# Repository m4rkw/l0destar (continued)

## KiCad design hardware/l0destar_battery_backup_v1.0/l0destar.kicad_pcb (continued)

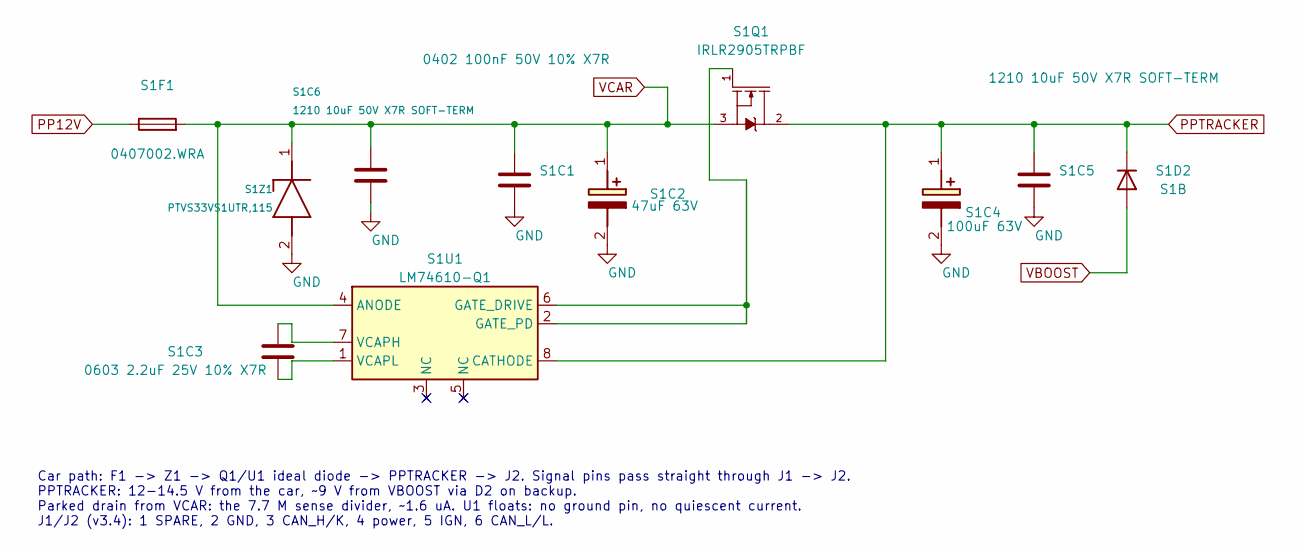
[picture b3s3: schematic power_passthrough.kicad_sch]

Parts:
S1C1: 0402 100nF 50V 10% X7R; C_0402_1005Metric; MPN GRM155R71H104KE14D
S1C2: 47uF 63V; EEE_FK1J470P; MPN EEE-FK1J470P
S1C3: 0603 2.2uF 25V 10% X7R; C_0603_1608Metric; MPN GRM188Z71E225KE43D
S1C4: 100uF 63V; EEEFK1J101P; MPN EEE-FK1J101P
S1C5, S1C6: 1210 10uF 50V X7R SOFT-TERM; C_1210_3225Metric; MPN MCJCU32MLB7106KPPDT1
S1D2: S1B; D_SMA; MPN S1B
S1F1: 0407002.WRA; Fuse_1206_3216Metric; MPN 0407002.WRA
S1Q1: IRLR2905TRPBF
S1U1: LM74610-Q1; VSSOP-8_3x3mm_P0.65mm; MPN LM74610QDGKRQ1
S1Z1: PTVS33VS1UTR,115; Nexperia_CFP3_SOD-123W; MPN PTVS33VS1UTR,115

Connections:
GND: S1C1.2, S1C2.2 (-), S1C4.2 (-), S1C5.2, S1C6.2, S1Z1.2 (A); also elsewhere on the board
unnamed: S1Q1.1, S1U1.2 (GATE_PD), S1U1.6 (GATE_DRIVE)
unnamed: S1C3.1, S1U1.7 (VCAPH)
unnamed: S1C3.2, S1U1.1 (VCAPL)
PP12V: S1F1.1; also elsewhere on the board
PPTRACKER: S1C4.1 (+), S1C5.1, S1D2.1 (K), S1Q1.2, S1Q1.PAD, S1U1.8 (CATHODE); also elsewhere on the board
VBOOST: S1D2.2 (A); also elsewhere on the board
VCAR: S1C1.1, S1C2.1 (+), S1C6.1, S1F1.2, S1Q1.3, S1U1.4 (ANODE), S1Z1.1 (K); also elsewhere on the board

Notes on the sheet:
Car path: F1 -> Z1 -> Q1/U1 ideal diode -> PPTRACKER -> J2. Signal pins pass straight through J1 -> J2. PPTRACKER: 12-14.5 V from the car, ~9 V from VBOOST via D2 on backup. Parked drain from VCAR: the 7.7 M sense divider, ~1.6 uA. U1 floats: no ground pin, no quiescent current. J1/J2 (v3.4): 1 SPA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

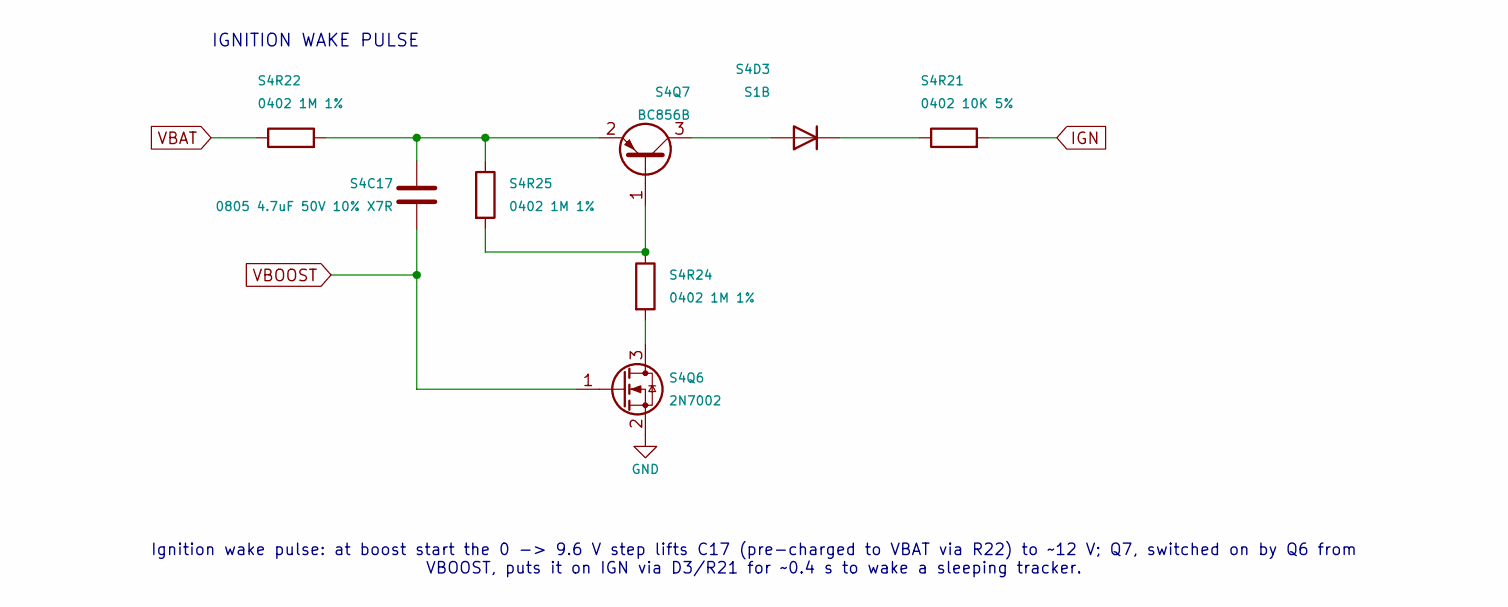
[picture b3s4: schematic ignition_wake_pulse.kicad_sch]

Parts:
S4C17: 0805 4.7uF 50V 10% X7R; C_0805_2012Metric; MPN GRM21BZ71H475KE15K
S4D3: S1B; D_SMA; MPN S1B
S4Q6: 2N7002; SOT-23; MPN 2N7002
S4Q7: BC856B; SOT-23; MPN BC856B
S4R21: 0402 10K 5%; R_0402_1005Metric
S4R22, S4R24, S4R25: 0402 1M 1%; R_0402_1005Metric

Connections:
GND: S4Q6.2 (S); also elsewhere on the board
IGN: S4R21.2; also elsewhere on the board
unnamed: S4D3.2 (A), S4Q7.3 (C)
unnamed: S4D3.1 (K), S4R21.1
unnamed: S4Q6.3 (D), S4R24.2
unnamed: S4Q7.1 (B), S4R24.1, S4R25.2
unnamed: S4C17.1, S4Q7.2 (E), S4R22.2, S4R25.1
VBAT: S4R22.1; also elsewhere on the board
VBOOST: S4C17.2, S4Q6.1 (G); also elsewhere on the board

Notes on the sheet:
IGNITION WAKE PULSE
Ignition wake pulse: at boost start the 0 -> 9.6 V step lifts C17 (pre-charged to VBAT via R22) to ~12 V; Q7, switched on by Q6 from VBOOST, puts it on IGN via D3/R21 for ~0.4 s to wake a sleeping tracker.

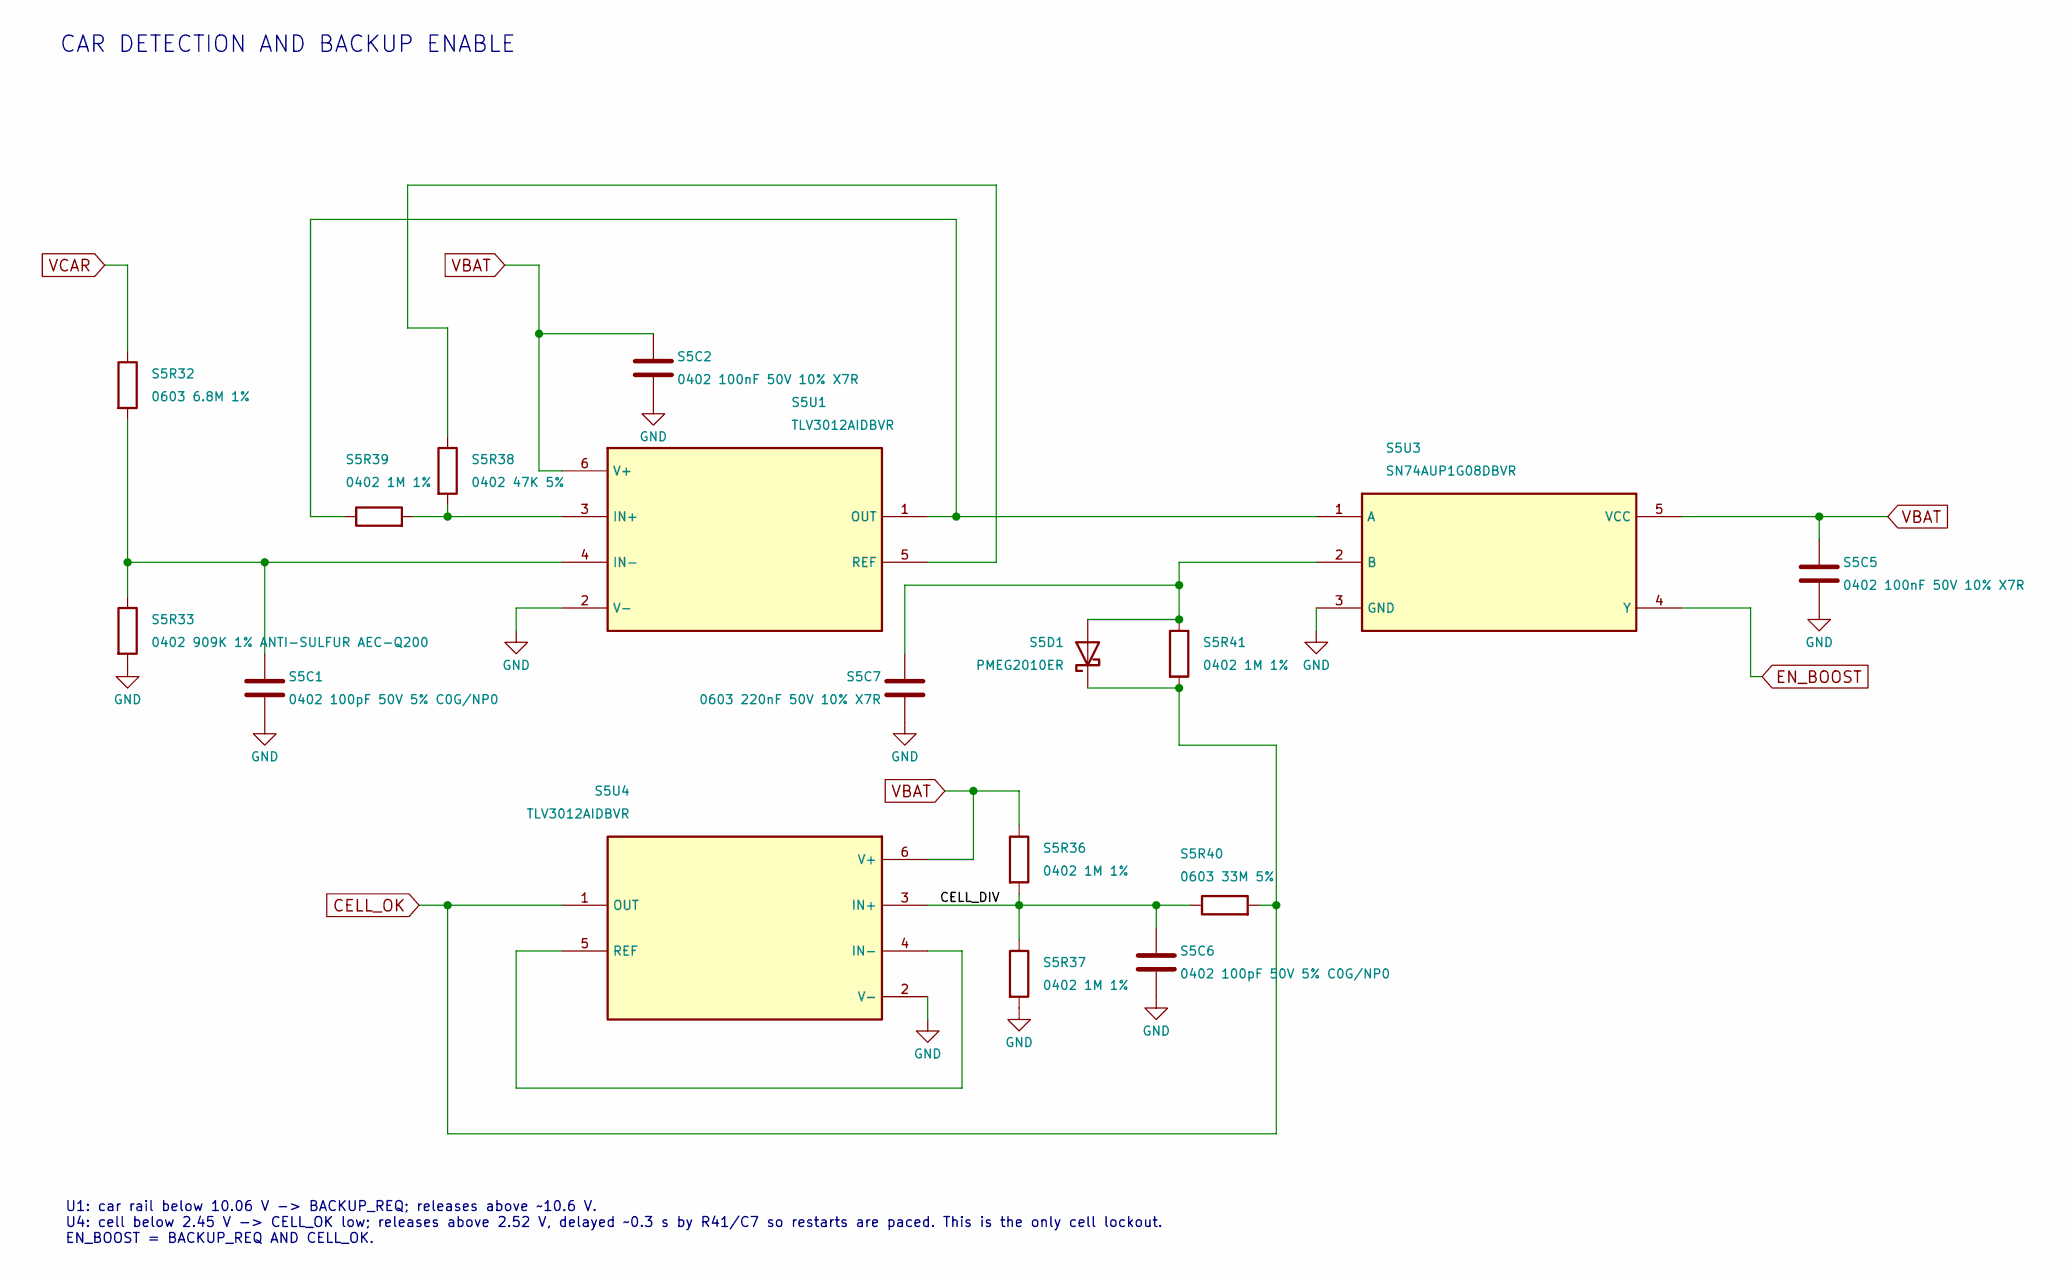
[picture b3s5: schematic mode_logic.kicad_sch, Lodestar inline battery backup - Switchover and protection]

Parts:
S5C1, S5C6: 0402 100pF 50V 5% C0G/NP0; C_0402_1005Metric; MPN 0402N101J500CT
S5C2, S5C5: 0402 100nF 50V 10% X7R; C_0402_1005Metric; MPN GRM155R71H104KE14D
S5C7: 0603 220nF 50V 10% X7R; C_0603_1608Metric
S5D1: PMEG2010ER; Nexperia_CFP3_SOD-123W; MPN PMEG2010ER,115
S5R32: 0603 6.8M 1%; R_0603_1608Metric
S5R33: 0402 909K 1% ANTI-SULFUR AEC-Q200; R_0402_1005Metric; MPN AF0402FR-07909KL
S5R36, S5R37, S5R39, S5R41: 0402 1M 1%; R_0402_1005Metric
S5R38: 0402 47K 5%; R_0402_1005Metric
S5R40: 0603 33M 5%; R_0603_1608Metric
S5U1, S5U4: TLV3012AIDBVR; SOT-23-6; MPN TLV3012AIDBVR
S5U3: SN74AUP1G08DBVR; SOT-23-5; MPN SN74AUP1G08DBVR

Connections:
/Automatic switchover/CELL_DIV: S5C6.1, S5R36.2, S5R37.1, S5R40.1, S5U4.3 (IN+)
CELL_OK: S5D1.1 (K), S5R40.2, S5R41.2, S5U4.1 (OUT)
EN_BOOST: S5U3.4 (Y); also elsewhere on the board
GND: S5C1.2, S5C2.2, S5C5.2, S5C6.2, S5C7.2, S5R33.2, S5R37.2, S5U1.2 (V-), S5U3.3 (GND), S5U4.2 (V-); also elsewhere on the board
unnamed: S5C7.1, S5D1.2 (A), S5R41.1, S5U3.2 (B)
unnamed: S5R38.2, S5R39.2, S5U1.3 (IN+)
unnamed: S5C1.1, S5R32.2, S5R33.1, S5U1.4 (IN-)
unnamed: S5R39.1, S5U1.1 (OUT), S5U3.1 (A)
unnamed: S5R38.1, S5U1.5 (REF)
unnamed: S5U4.4 (IN-), S5U4.5 (REF)
VBAT: S5C2.1, S5C5.1, S5R36.1, S5U1.6 (V+), S5U3.5 (VCC), S5U4.6 (V+); also elsewhere on the board
VCAR: S5R32.1; also elsewhere on the board

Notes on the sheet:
CAR DETECTION AND BACKUP ENABLE
U1: car rail below 10.06 V -> BACKUP_REQ; releases above ~10.6 V. U4: cell below 2.45 V -> CELL_OK low; releases above 2.52 V, delayed ~0.3 s by R41/C7 so restarts are paced. This is the only cell lockout. EN_BOOST = BACKUP_REQ AND CELL_OK.

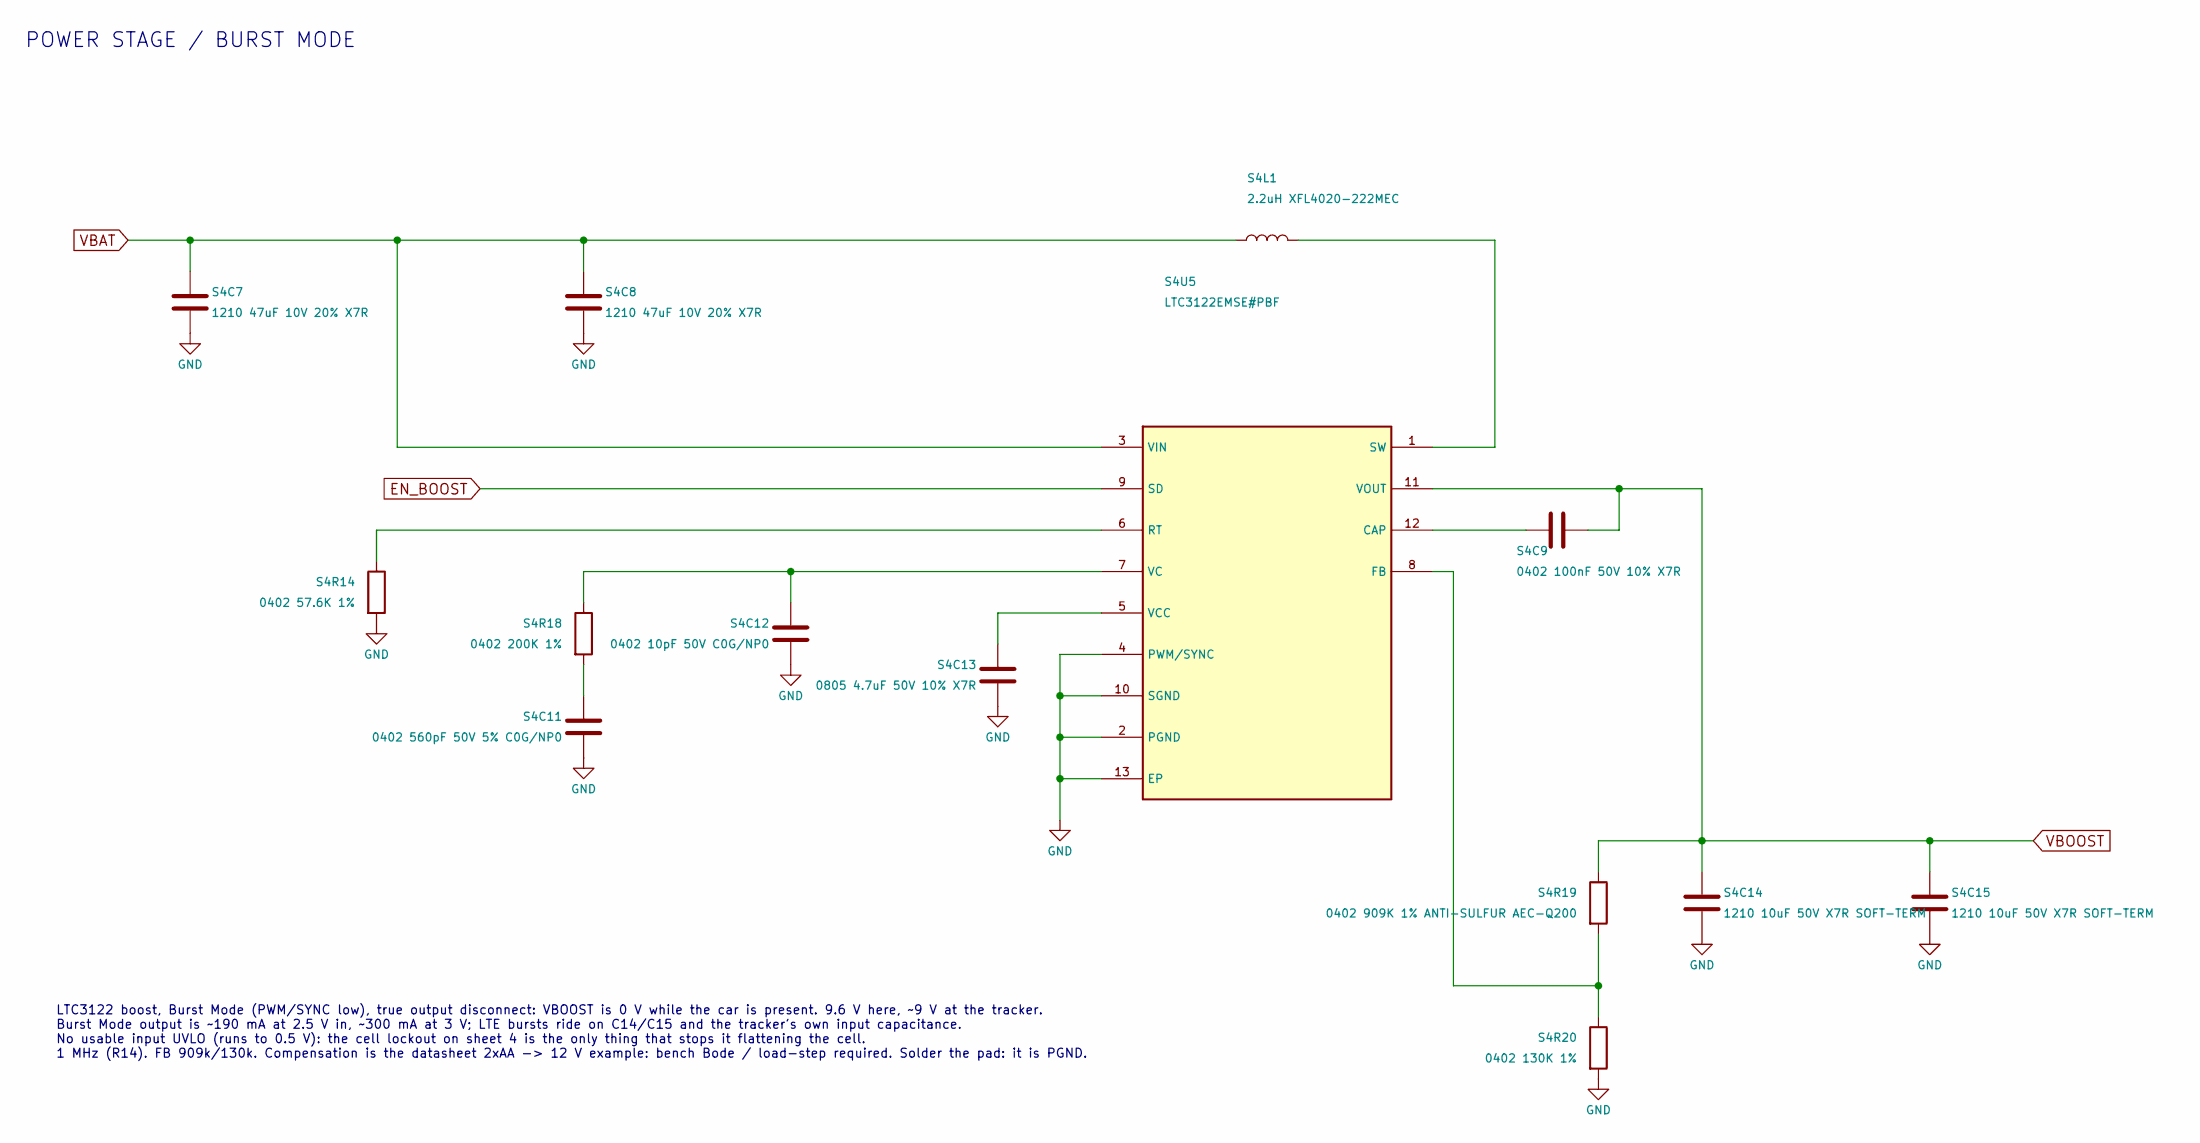
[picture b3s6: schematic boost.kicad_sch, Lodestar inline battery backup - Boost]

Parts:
S4C7, S4C8: 1210 47uF 10V 20% X7R; C_1210_3225Metric; MPN CL32B476MPJNNNE
S4C9: 0402 100nF 50V 10% X7R; C_0402_1005Metric; MPN GRM155R71H104KE14D
S4C11: 0402 560pF 50V 5% C0G/NP0; C_0402_1005Metric
S4C12: 0402 10pF 50V C0G/NP0; C_0402_1005Metric; MPN GRM1555C1H100JA01D
S4C13: 0805 4.7uF 50V 10% X7R; C_0805_2012Metric; MPN GRM21BZ71H475KE15K
S4C14, S4C15: 1210 10uF 50V X7R SOFT-TERM; C_1210_3225Metric; MPN MCJCU32MLB7106KPPDT1
S4L1: 2.2uH XFL4020-222MEC; IND_XFL4020-222ME; MPN XFL4020-222MEC
S4R14: 0402 57.6K 1%; R_0402_1005Metric
S4R18: 0402 200K 1%; R_0402_1005Metric
S4R19: 0402 909K 1% ANTI-SULFUR AEC-Q200; R_0402_1005Metric; MPN AF0402FR-07909KL
S4R20: 0402 130K 1%; R_0402_1005Metric
S4U5: LTC3122EMSE#PBF; MSOP-12-1EP_3x4.039mm_P0.65mm_EP1.651x2.845mm; MPN LTC3122EMSE#PBF

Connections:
EN_BOOST: S4U5.9 (SD); also elsewhere on the board
GND: S4C7.2, S4C8.2, S4C11.2, S4C12.2, S4C13.2, S4C14.2, S4C15.2, S4R14.2, S4R20.2, S4U5.2 (PGND), S4U5.4 (PWM/SYNC), S4U5.10 (SGND), S4U5.13 (EP); also elsewhere on the board
unnamed: S4C11.1, S4R18.2
unnamed: S4C9.1, S4U5.12 (CAP)
unnamed: S4R19.2, S4R20.1, S4U5.8 (FB)
unnamed: S4R14.1, S4U5.6 (RT)
unnamed: S4L1.2, S4U5.1 (SW)
unnamed: S4C12.1, S4R18.1, S4U5.7 (VC)
unnamed: S4C13.1, S4U5.5 (VCC)
VBAT: S4C7.1, S4C8.1, S4L1.1, S4U5.3 (VIN); also elsewhere on the board
VBOOST: S4C9.2, S4C14.1, S4C15.1, S4R19.1, S4U5.11 (VOUT); also elsewhere on the board

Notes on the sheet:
LTC3122 boost, Burst Mode (PWM/SYNC low), true output disconnect: VBOOST is 0 V while the car is present. 9.6 V here, ~9 V at the tracker. Burst Mode output is ~190 mA at 2.5 V in, ~300 mA at 3 V; LTE bursts ride on C14/C15 and the tracker's own input capacitance. No usable input UVLO (runs to 0.5 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
POWER STAGE / BURST MODE

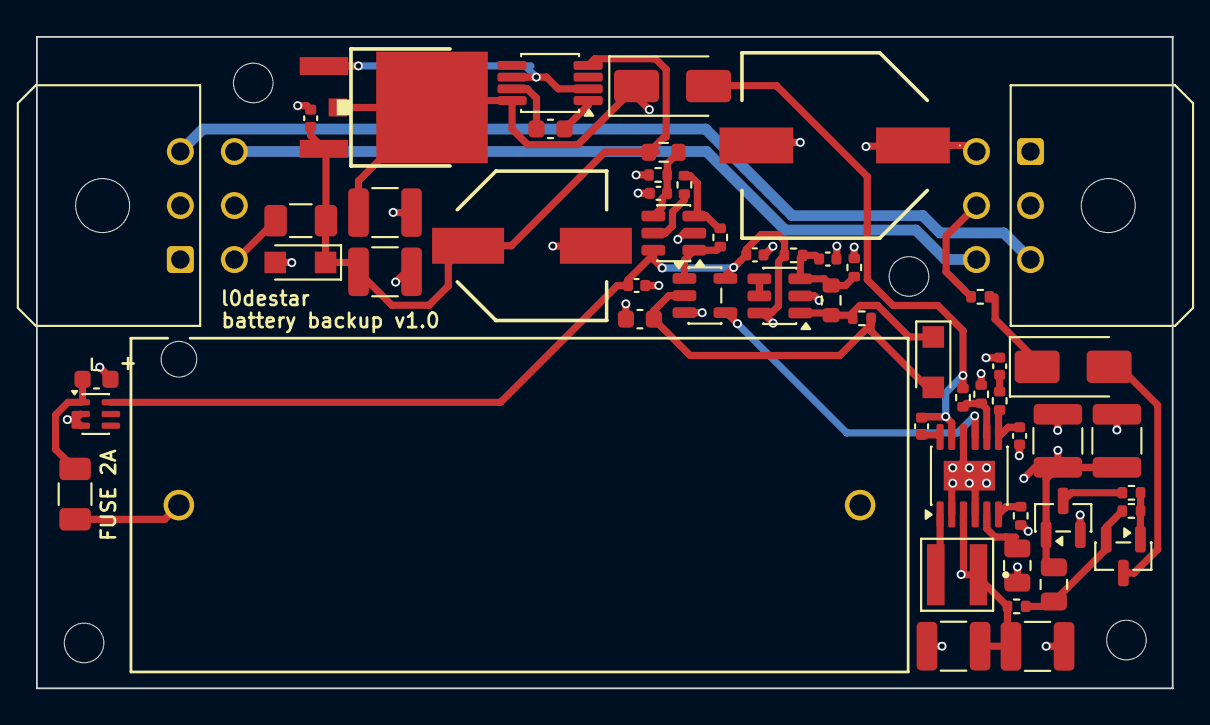
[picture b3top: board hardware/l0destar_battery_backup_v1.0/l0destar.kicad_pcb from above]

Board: 4 copper layers, 63.1 x 36.2 mm, 60 parts (0 on the bottom side), 35 nets.

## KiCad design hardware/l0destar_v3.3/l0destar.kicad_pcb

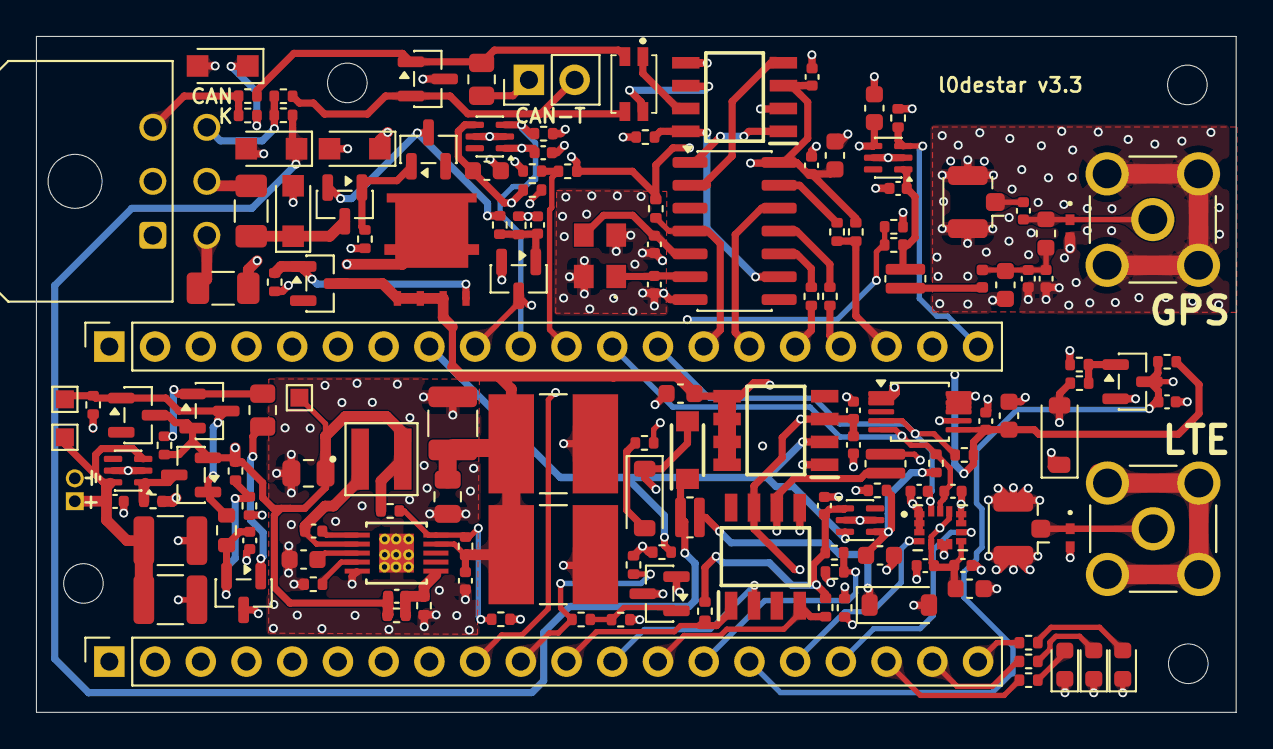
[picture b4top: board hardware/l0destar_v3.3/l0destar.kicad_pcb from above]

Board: 4 copper layers, 66.7 x 37.5 mm, 156 parts (0 on the bottom side), 85 nets.

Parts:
H1, H2, H3, H4: MountingHole; MountingHole_2.2mm_M2
S1C1, S3C2, S4C1, S6C1, S6C8, S7C2, S7C4, S7C9, S8C1, S8C3, S9C1, S9C4, S10C1: 0402 100nF 50V 10% X7R; C_0402_1005Metric
S1J1: Main connector; Molex_Micro-Fit_3.0_43045-0600_2x03_P3.00mm_Horizontal
S1J2: Conn_01x20_Socket; MakerDiary_nRF9151_ConnectKit_PinHeader_1-20_tight
S1J3: Conn_01x20_Socket_21-40; MakerDiary_nRF9151_ConnectKit_PinHeader_21-40
S1J4: +; Makerdiary_power_header
S1R1, S1R2: 0402 1.8K 1%; R_0402_1005Metric
S1R3, S1R4, S1R5, S2R2, S7R1, S7R3, S7R6, S7R7, S7R8, S10R6: 0402 100K 5%; R_0402_1005Metric
S2C1, S2C2: 47uF 2220 50V 20% X7R; CAPC6050X550N
S2C3: 10uF 1210 50V 10% X7R SOFT TERMINATION; C_1210_3225Metric
S2D1, S2D3, S11D1: BZX84C15; SOT-23
S2D2, S2D4, S10D2, S10D4: PTVS33VS1UTR,115; Nexperia_CFP3_SOD-123W
S2F1, S2F2: 0407002.WRA; Fuse_1206_3216Metric
S2Q1, S11Q1: SQ2361CES-T1_BE3; SOT-23
S2Q2: SQJ457EP-T1_BE3; POWERPAK-SO-8-4
S2R1, S7R2, S7R4, S7R9: 0402 1M 5%; R_0402_1005Metric
S3C1, S6C2, S7C1, S7C3, S7C8, S15C4: 0603 2.2uF 25V 10% X7R; C_0603_1608Metric
S3U1: INA228; TSSOP-10_3x3mm_P0.5mm
S4Q1, S7Q1, S10Q1: 2N7002; SOT-23
S4R1, S7R5: 0402 180K 5%; R_0402_1005Metric
S4R2, S4R3: 0402 56K 5%; R_0402_1005Metric
S5R1, S5R2, S5R3, S5R4, S5R5: 0402 0R; R_0402_1005Metric
S6C3: 0805 4.7uF 50V 10% X7R; C_0805_2012Metric
S6C4: 0402 10pF 50V C0G/NP0; C_0402_1005Metric
S6C5: 0805 22uF 10V 20% X7R; C_0805_2012Metric
S6L1: XFL4020-222ME; IND_XFL4020-222ME
S6R1: 0402 18.2K 1%; R_0402_1005Metric
S6R2: 0402 226K 1% ANTI-SULFUR AEC-Q200; R_0402_1005Metric
S6R3, S6R4, S10R9, S11R5: 0402 1M 1% ANTI-SULFUR AEC-Q200; R_0402_1005Metric
S6R5: 0402 243K 1% ANTI-SULFUR AEC-Q200; R_0402_1005Metric
S6R6: 0402 3.92M 1%; R_0402_1005Metric
S6U1: LT8609AIMSE_PBF; LT8609AIMSE_WITH_GROUND_VIAS
S7C5, S7C7: 0402 1nF 50V 10% X7R; C_0402_1005Metric
S7C6: 0603 220nF 50V 10% X7R; C_0603_1608Metric
S7U1, S7U2, S7U4: SiP32431DR3; SOT-363_SC-70-6
S7U3: ITS4060SSJNXUMA1
S8C2, S9C5: 0603 10uF 10V 20% X7R; C_0603_1608Metric
S8C4, S8C5, S15C2: 0402 100pF 50V 5% C0G/NP0; C_0402_1005Metric
S8R1: 0402 FB BLM15AG601SH1D; R_0402_1005Metric
S8U1: ASM330LHHXTR; XDCR_ASM330LHHXTR
S9C2, S9C3: 0402 27pF 10V 5% C0G/NP0; C_0402_1005Metric
S9D1: NUP2105L; SOT-23
S9FL1: ACT1210-101-2P-TL00; ACT12101012PTL00_tight
S9J1: Conn_01x02_Pin; PinHeader_1x02_P2.54mm_Vertical_Tight
S9R1, S9R2, S9R4, S10R1, S10R2, S10R5: 0402 10K 5%; R_0402_1005Metric
S9R3: 0805 120R 5% 0.5W; R_0805_2012Metric
S9R5, S13R1, S13R2, S13R3: 0402 1K 5%; R_0402_1005Metric
S9R6, S9R7: 0402 220R 5%; R_0402_1005Metric
S9U1: MAX33041EASA+; SOIC127P600X175-8N
S9U2: MCP2518FD-xQBB; SOIC-14_3.9x8.7mm_P1.27mm
S9Y1: ECS-400-18-33-JGN-TR3; ECS4001833JGNTR3
S10D1, S10D3, S10D5: 1N4148W; D_SOD-123
S10R3, S10R4: 0508 510R 5% 1W; R_0508_1220Metric_WideTerminal_Tight
S10R7, S10R8: 0402 47K 5%; R_0402_1005Metric
S10U1: TJA1027T_20,118; TJA1027T_20_118
S10U2: AL5809-90P1-7
S11C1, S11C2: 1210 47uF 10V 20% X7R; C_1210_3225Metric
S11C3: 0402 3.3pF 50V C0G/NP0 +/- 0.25pF; C_0402_1005Metric
S11Q2: BC856BLT1G; SOT-23
S11R1: 0402 10K 1%; R_0402_1005Metric
S11R2: 0402 1M 1%; R_0402_1005Metric
S11R3: 0603 33M 5%; R_0603_1608Metric
S11R4: 0805 15K 1% ANTI-SULFUR AEC-Q200; R_0805_2012Metric
S11R6: 0402 1.05M 1%; R_0402_1005Metric
S11TP1: TestPoint - fault injection; TestPoint_Pad_1.0x1.0mm
S11U1: LM66100DCK; SOT-363_SC-70-6
S11U2: ATL431BQDBZR; SOT-23
S12TP6: 4.2V protected; TestPoint_Pad_1.0x1.0mm
S12TP7: 4.2V unprotected; TestPoint_Pad_1.0x1.0mm
S13D1, S13D2, S13D3: Wurth 150060RS86000; LED_0603_1608Metric
S15C1: 0402 47pF 50V 5% C0G/NP0; C_0402_1005Metric
S15C3: 0402 10nF 50V 5% C0G/NP0; C_0402_1005Metric
S15D1, S15D2: TPD1E05U06DPYR; DIO_TPD1E05U06DPYR
S15FB1: 0402 600R 0.5A 25%; L_0402_1005Metric
S15J1: GPS_UFL; U.FL_Hirose_U.FL-R-SMT-1_Vertical
S15J2: GPS_SMA; SAMTEC_SMA-J-P-H-RA-TH1_centrepin
S15J3: GSM_UFL; U.FL_Hirose_U.FL-R-SMT-1_Vertical
S15J4: GSM_SMA; SAMTEC_SMA-J-P-H-RA-TH1_centrepin
S15L1: LQW18AN68NJ00D; L_0603_1608Metric
S15R1: 0508 1W 5% 15R; R_0508_1220Metric_WideTerminal_Tight

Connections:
ACCELL_INT1: S1J2.16, S8U1.4 (INT1)
ACCELL_INT2: S1J2.17, S8U1.9 (INT2)
CAN_CS: S1J3.23 (Pin_18), S9R1.2, S9R5.1
CAN_ENABLE: S1J3.31 (Pin_10), S1R4.2, S7U2.3 (ON)
CAN_H: S5R1.2, S9D1.1 (K), S9FL1.2, S9R3.2
CAN_H_ISO9141_K: S1J1.3, S5R1.1, S5R2.1
CAN_INT: S1J3.27 (Pin_14), S9R2.2, S9U2.4 (~INT)
CAN_L: S5R3.2, S9D1.2 (K), S9FL1.3, S9J1.2
CAN_L_ISO9141_L: S1J1.6, S5R3.1, S5R4.1
CAN_SCK: S1J3.25 (Pin_16), S9R6.1
CAN_SDI: S1J3.24 (Pin_17), S9R7.1
CAN_SDO: S1J3.26 (Pin_15), S9U2.12 (SDO)
GND: S1C1.1, S1J1.2, S1J2.3 (GND), S1J3.39 (Pin_2), S1J4.2, S1R3.1, S1R4.1, S1R5.1, S2C1.2, S2C2.2, S2C3.2, S2D2.2 (A), S2D4.2 (A), S2R1.2, S2R2.2, S3C1.1, S3C2.1, S3U1.1 (A1), S3U1.2 (A0), S3U1.7 (GND), S4C1.2, S4Q1.2 (S), S4R2.1, S6C2.2, S6C3.2, S6C5.2, S6C8.2, S6R1.2, S6R2.2, S6R5.1, S6U1.5 (SYNC), S6U1.11 (GND), S7C1.2, S7C2.2, S7C3.2, S7C4.2, S7C5.2, S7C6.2, S7C7.2, S7C8.2, S7C9.2, S7Q1.2 (S), S7R2.1, S7R4.1, S7R6.1, S7R9.1, S7U1.2 (GND), S7U1.5 (GND), S7U2.2 (GND), S7U2.5 (GND), S7U3.1 (GND), S7U4.2 (GND), S7U4.5 (GND), S8C1.2, S8C2.2, S8C3.2, S8C4.2, S8C5.2, S8U1.1 (SDO/SA0), S8U1.2 (MSDA), S8U1.3 (MSCL), S8U1.6 (NC), S8U1.7 (GND), S8U1.10 (NC), S8U1.11 (NC), S9C1.2, S9C2.2, S9C3.2, S9C4.2, S9C5.2, S9D1.3 (A), S9R4.2, S9U1.2 (GND), S9U1.5 (SHDN), S9U2.7 (VSS), S9Y1.2 (GND_1), S9Y1.4 (GND_2), S10C1.1, S10D2.2 (A), S10D4.2 (A), S10Q1.2 (S), S10R5.2, S10R6.1, S10R9.1, S10U1.5 (GND), S11C1.2, S11C2.2, S11C3.1, S11R2.1, S11R6.1, S11U1.2 (GND), S11U1.5 (ST), S11U2.3 (ANODE), S13D1.1 (K), S13D2.1 (K), S13D3.1 (K), S15C2.2, S15C3.2, S15C4.2, S15D1.2 (GND), S15D2.2 (GND), S15J1.2 (Ext), S15J2.2, S15J2.3, S15J2.4, S15J2.5, S15J3.2 (Ext), S15J4.2, S15J4.3, S15J4.4, S15J4.5
GPS_ENABLE: S1J3.21 (Pin_20), S1R3.2, S7U1.3 (ON)
I2C_SCL: S1J3.29 (Pin_12), S1R2.1, S3U1.5 (SCL), S8C5.1, S8U1.13 (SCL)
I2C_SDA: S1J3.28 (Pin_13), S1R1.1, S3U1.4 (SDA), S8C4.1, S8U1.14 (SDA)
IGN_SENSE: S1J3.32 (Pin_9), S4Q1.3 (D), S4R3.2
ISO9141_K: S5R2.2, S10D2.1 (K), S10R3.2, S10U1.6 (LIN)
ISO9141_L: S5R4.2, S10D4.1 (K), S10R4.2, S10U2.1 (IN)
K_ENABLE: S1J3.33 (Pin_8), S1R5.2, S7U3.2 (IN), S7U4.3 (ON)
K_RX: S1J2.11, S10R1.2, S10U1.1 (RXD)
K_SLEEP: S1J2.12, S10R6.2, S10U1.2 (SLP_N)
K_TX: S1J2.13, S10R2.2, S10U1.4 (TXD)
LED1: S1J2.18, S13R1.2
LED2: S1J2.19, S13R2.2
LED3: S1J2.20, S13R3.2
L_SEND: S1J2.10, S10R5.1, S10R7.1
L_SENSE: S1J3.22 (Pin_19), S10R8.1
unnamed: S2D1.1 (A), S2Q1.1 (G), S2R1.1
unnamed: S2D2.1 (K), S2F1.1, S2Q1.3 (D)
unnamed: S2D3.1 (A), S2Q2.4, S2R2.1
unnamed: S2D4.1 (K), S2F2.2, S2Q2.5_0, S2Q2.5_1, S2Q2.5_2, S2Q2.5_3
unnamed: S4C1.1, S4Q1.1 (G), S4R1.2, S4R2.2
unnamed: S6C1.1, S6U1.1 (BST)
unnamed: S6R4.1, S6R5.2, S6R6.2, S6U1.10 (EN/UV)
unnamed: S6C4.1, S6R2.1, S6R3.1, S6U1.6 (FB)
unnamed: S6C2.1, S6U1.3 (INTVCC)
unnamed: S6R1.1, S6U1.4 (RT)
unnamed: S6C1.2, S6L1.1, S6U1.2 (SW)
unnamed: S7Q1.1 (G), S7R5.2, S7R6.2
unnamed: S8C1.1, S8C2.1, S8C3.1, S8R1.2, S8U1.5 (VDD_IO), S8U1.8 (VDD), S8U1.12 (CS)
unnamed: S9J1.1, S9R3.1
unnamed: S9FL1.1, S9U1.7 (CANH)
unnamed: S9FL1.4, S9U1.6 (CANL)
unnamed: S9U1.4 (RXD), S9U2.2 (RXCAN)
unnamed: S9R4.1, S9U1.8 (STBY), S9U2.9 (~INT0/GPIO0/XSTBY)
unnamed: S9U1.1 (TXD), S9U2.1 (TXCAN)
unnamed: S9C3.1, S9U2.6 (OSC1), S9Y1.1 (IN/OUT)
unnamed: S9C2.1, S9U2.5 (OSC2), S9Y1.3 (OUT/IN)
unnamed: S9R6.2, S9U2.10 (SCK)
unnamed: S9R7.2, S9U2.11 (SDI)
unnamed: S9R5.2, S9U2.13 (~CS)
unnamed: S10D1.1 (K), S10R3.1
unnamed: S10D3.1 (K), S10R4.1
unnamed: S10D5.2 (A), S10R8.2
unnamed: S10D5.1 (K), S10Q1.3 (D), S10U2.2 (OUT)
unnamed: S10Q1.1 (G), S10R7.2, S10R9.2
unnamed: S11D1.1 (A), S11Q1.1 (G), S11Q2.3, S11R2.2, S11R3.2, S11TP1.1 (1_1)
unnamed: S11Q2.1, S11R1.1, S11R4.2
unnamed: S11R4.1, S11U2.1 (CATHODE)
unnamed: S11C3.2, S11R3.1, S11R5.2, S11R6.2, S11U2.2 (REF)
unnamed: S13D1.2 (A), S13R1.1
unnamed: S13D2.2 (A), S13R2.1
unnamed: S13D3.2 (A), S13R3.1
unnamed: S15C2.1, S15C3.1, S15C4.1, S15FB1.2, S15L1.1
unnamed: S15D1.1 (I/O), S15J3.1 (In), S15J4.1
unnamed: S15FB1.1, S15R1.1
unnamed: S15C1.1, S15J1.1 (In)
PP3V3: S1J3.40 (Pin_1), S1R1.2, S1R2.2, S3C1.2, S3C2.2, S3U1.6 (VS), S4R3.1, S7C1.1, S7C3.1, S7C8.1, S7R7.2, S7U1.4 (IN), S7U2.4 (IN), S7U4.4 (IN), S8R1.1
PP3V3_CAN: S7C4.1, S7R3.1, S7U2.1 (OUT), S9C1.1, S9C4.1, S9C5.1, S9R1.1, S9R2.1, S9U1.3 (VDD), S9U2.14 (VDD)
PP3V3_CAN_ST: S1J3.30 (Pin_11), S7R3.2, S7R4.2
PP3V3_GPS: S7C2.1, S7R1.1, S7U1.1 (OUT), S15R1.2
PP3V3_GPS_ST: S1J2.9, S7R1.2, S7R2.2
PP3V3_K: S7C9.1, S7R8.1, S7U4.1 (OUT), S10R1.1, S10R2.1
PP3V3_K_ST: S1J2.14, S7R8.2, S7R9.2
PP4V2: S1C1.2, S1J4.1, S11C1.1, S11C2.1, S11U1.3 (~CE), S11U1.6 (VOUT), S12TP6.1 (1_1)
PP4V2_OVP_PROTECTED: S5R5.2, S11Q1.3 (D), S11U1.1 (VIN)
PP4V2_UNPROTECTED: S5R5.1, S6C4.2, S6C5.1, S6L1.2, S6R3.2, S6R6.1, S11D1.3 (K), S11Q1.2 (S), S11Q2.2, S11R1.2, S11R5.1, S12TP7.1 (1_1)
PP12V: S1J1.4, S2F2.1
PP12VI: S1J1.5, S2F1.2
PP12VIP: S2D1.3 (K), S2Q1.2 (S), S4R1.1
PP12VP: S2C1.1, S2C2.1, S2C3.1, S2D3.3 (K), S2Q2.1, S2Q2.2, S2Q2.3, S3U1.8 (Vbus), S3U1.9 (Vin-), S3U1.10 (Vin+), S6C3.1, S6C8.1, S6R4.2, S6U1.9 (VIN), S7C6.1, S7U3.5 (VS_1), S7U3.6 (VS_2), S7U3.7 (VS_3), S7U3.8 (VS_4)
PP12V_K: S7C5.1, S7R5.1, S7U3.3 (OUT), S10C1.2, S10D1.2 (A), S10D3.2 (A), S10U1.7 (VBAT)
PP12V_K_ST: S1J2.15, S7C7.1, S7Q1.3 (D), S7R7.1
RF: S15C1.2, S15D2.1 (I/O), S15J2.1, S15L1.2
